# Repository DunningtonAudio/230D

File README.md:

# 230D
A triple envelope follower project

The 230D Triple Envelope Follower is designed to replicate the functionality of the Buchla 230A module using modern construction techniques and readily available parts. It is primarily based on the original circuit designed by Don Buchla, with the following additions/alterations:

* Proper current limiting implemented for pulse output LEDs, increasing LED life and preventing crosstalk between channels
* Pulse/gate output voltages adjusted to 10V/5V
* Pulse outputs are buffered, protecting the passive pulse generation network from the effects of loading when stacking one output to multiple destinations
* Pulse outputs are designed to allow stacking of multiple outputs to a single input, whilst also being able to drive a floating input low.

The repository contains:

* KiCad project files
* Schematic and build/calibration notes as PDF files
* Bill of Materials in ODS and PDF format
* Interactive webpage for matching BOM items to PCB locations

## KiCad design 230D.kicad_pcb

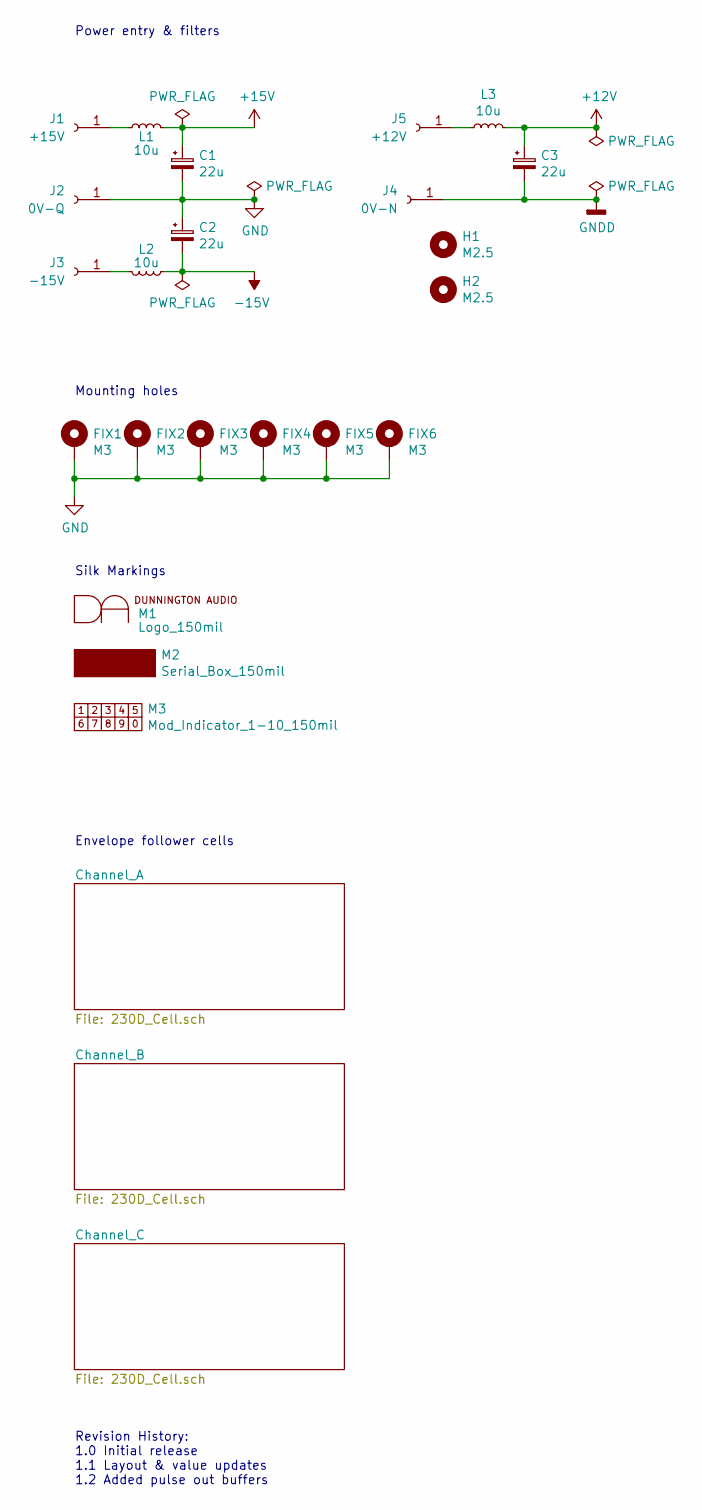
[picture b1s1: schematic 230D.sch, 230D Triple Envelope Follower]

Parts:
C1, C2, C3: 22u; CP_Elec_5x5.3
FIX1, FIX2, FIX3, FIX4, FIX5, FIX6: M3; MountingHole_3.2mm_M3_Pad_Via
H1, H2: M2.5; MountingHole_2.5mm
J1: +15V; SolderWirePad_1x01_Drill1.2mm
J2: 0V-Q; SolderWirePad_1x01_Drill1.2mm
J3: -15V; SolderWirePad_1x01_Drill1.2mm
J4: 0V-N; SolderWirePad_1x01_Drill1.2mm
J5: +12V; SolderWirePad_1x01_Drill1.2mm
L1, L2, L3: 10u; L_0805_2012Metric
M1: Logo_150mil
M2: Serial_Box_150mil
M3: Mod_Indicator_1-10_150mil

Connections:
+12V: C3.1, L3.2; also elsewhere on the board
+15V: C1.1, L1.2; also elsewhere on the board
-15V: C2.2, L2.1; also elsewhere on the board
GND: C1.2, C2.1, FIX1.1, FIX2.1, FIX3.1, FIX4.1, FIX5.1, FIX6.1, J2.1; also elsewhere on the board
GNDD: C3.2, J4.1; also elsewhere on the board
unnamed: J1.1, L1.1
unnamed: J3.1, L2.2
unnamed: J5.1, L3.1

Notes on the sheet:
Power entry & filters
Mounting holes
Silk Markings
Envelope follower cells
Revision History: 1.0 Initial release 1.1 Layout & value updates 1.2 Added pulse out buffers

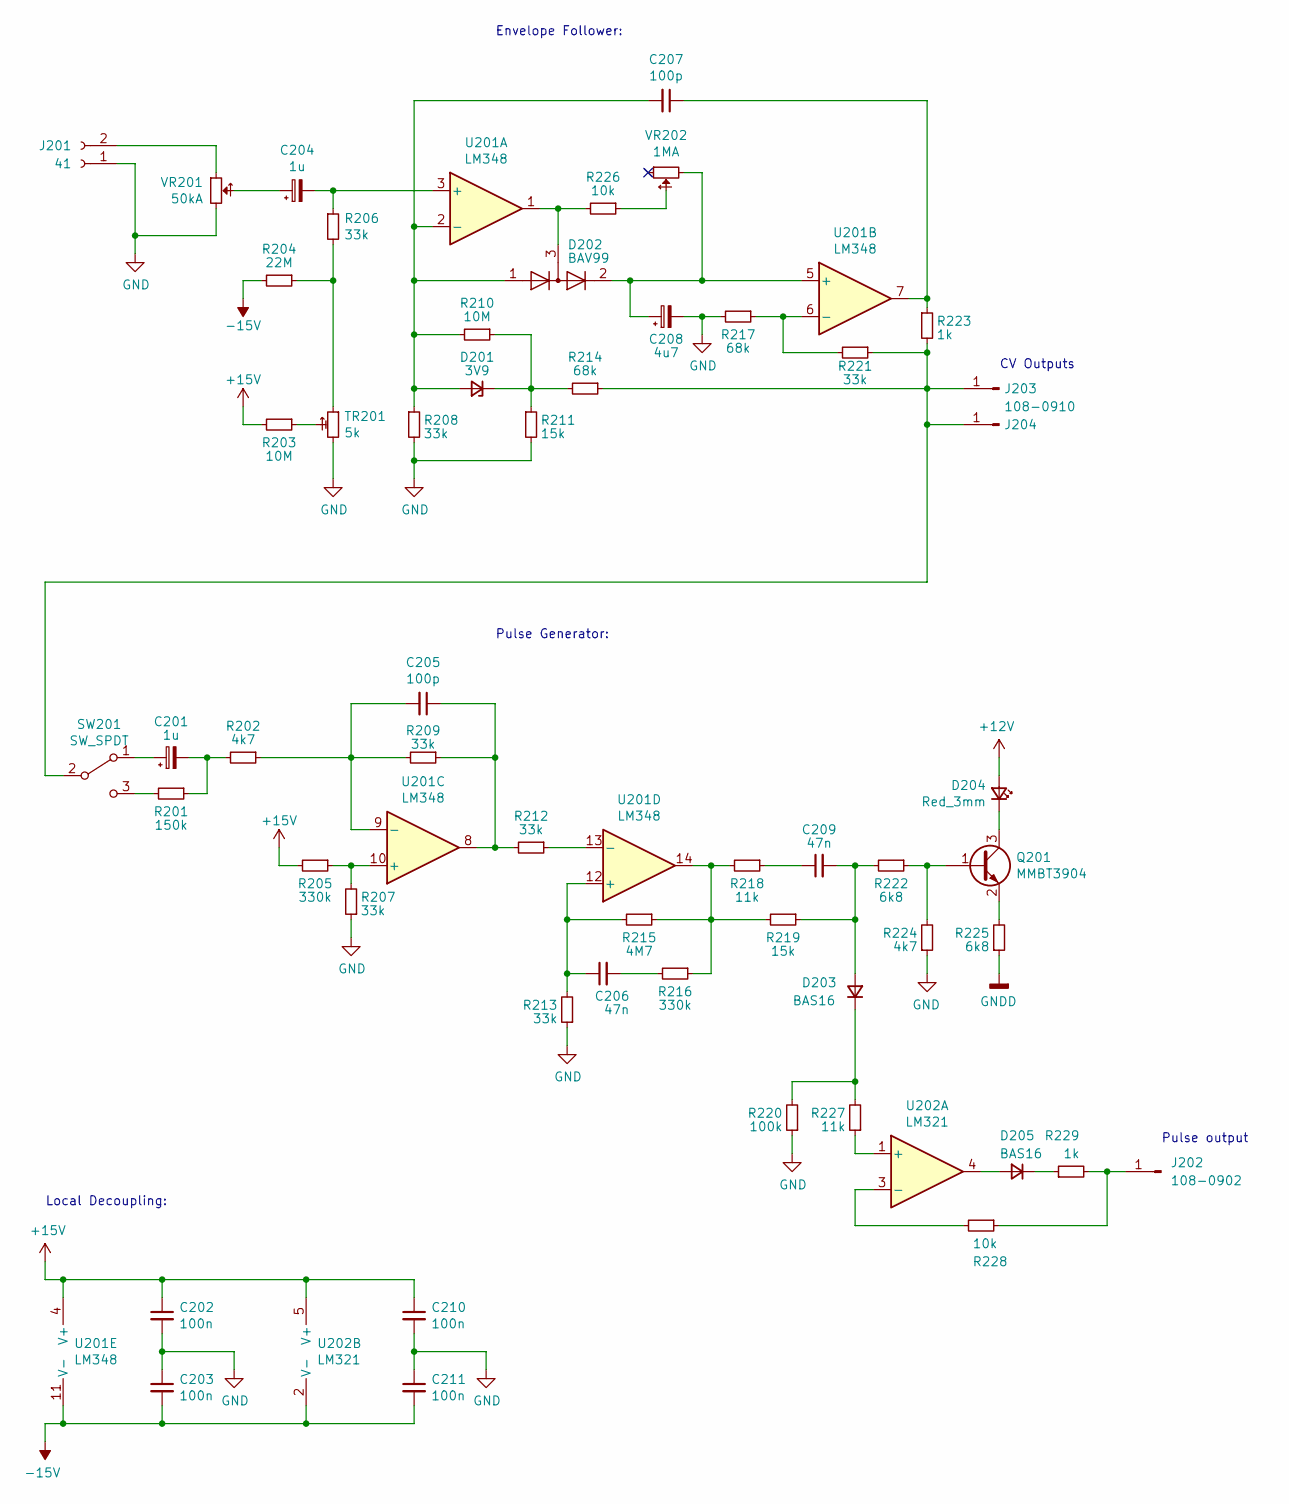
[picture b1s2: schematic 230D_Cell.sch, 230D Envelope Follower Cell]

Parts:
C101, C104: 1u; CP_Elec_4x5.3
C102, C103, C110, C111: 100n; C_0805_2012Metric
C105, C107: 100p; C_0805_2012Metric
C106, C109: 47n; C_0805_2012Metric
C108: 4u7; CP_EIA-3528-21_Kemet-B
D101: 3V9; D_SOD-323
D102: BAV99; SOT-23
D103, D105: BAS16; SOT-23
D104: Red_3mm; LED_D3.0mm
J101: 41; Switchcraft_41
J102: 108-0902; Johnson_108-09XX-001
J103, J104: 108-0910; Johnson_108-09XX-001
Q101: MMBT3904; SOT-23
R101: 150k; R_0805_2012Metric
R102, R124: 4k7; R_0805_2012Metric
R103, R110: 10M; R_0805_2012Metric
R104: 22M; R_0805_2012Metric
R105, R116: 330k; R_0805_2012Metric
R106, R107, R108, R109, R112, R113, R121: 33k; R_0805_2012Metric
R111, R119: 15k; R_0805_2012Metric
R114, R117: 68k; R_0805_2012Metric
R115: 4M7; R_0805_2012Metric
R118, R127: 11k; R_0805_2012Metric
R120: 100k; R_0805_2012Metric
R122, R125: 6k8; R_0805_2012Metric
R123, R129: 1k; R_0805_2012Metric
R126, R128: 10k; R_0805_2012Metric
SW101: SW_SPDT; M201xSS1x01
TR101: 5k; Potentiometer_Bourns_3314J_Vertical
U101: LM348; SOIC-14_3.9x8.7mm_P1.27mm
U102: LM321; SOT-23-5
VR101: 50kA; RV16AF-41-(L)R1-XXX
VR102: 1MA; RV16AF-41-(L)R1-XXX

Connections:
+12V: D104.2 (A); also elsewhere on the board
+15V: C102.1, C110.1, R103.2, R105.2, U101.4 (V+), U102.5 (V+); also elsewhere on the board
-15V: C103.2, C111.2, R104.2, U101.11 (V-), U102.2 (V-); also elsewhere on the board
GND: C102.2, C103.1, C108.2, C110.2, C111.1, J101.1, R107.1, R108.2, R111.2, R113.1, R117.2, R120.1, R124.1, TR101.1, VR101.1; also elsewhere on the board
GNDD: R125.1; also elsewhere on the board
unnamed: C101.1, SW101.1 (A)
unnamed: C101.2, R101.1, R102.2
unnamed: C104.1, VR101.2
unnamed: C104.2, R106.1, U101.3 (+)
unnamed: C105.1, R109.1, R112.2, U101.8
unnamed: C105.2, R102.1, R109.2, U101.9 (-)
unnamed: C106.1, R113.2, R115.2, U101.12 (+)
unnamed: C106.2, R116.2
unnamed: C107.1, R123.1, U101.7
unnamed: C107.2, D101.2 (A), D102.1 (K), R108.1, R110.2, U101.2 (-)
unnamed: C108.1, D102.2 (A), U101.5 (+), VR102.1
unnamed: C109.1, R118.1
unnamed: C109.2, D103.1 (A), R119.1, R122.2
unnamed: D101.1 (K), R110.1, R111.1, R114.2
unnamed: D102.3 (K), R126.2, U101.1
unnamed: D103.3 (K), R120.2, R127.2
unnamed: D104.1 (K), Q101.3 (C)
unnamed: D105.1 (A), U102.4
unnamed: D105.3 (K), R129.1
unnamed: J101.2, VR101.3
unnamed: J102.1, R128.1, R129.2
unnamed: J103.1, J104.1, R114.1, R121.1, R123.2, SW101.2 (B)
unnamed: Q101.1 (B), R122.1, R124.2
unnamed: Q101.2 (E), R125.2
unnamed: R101.2, SW101.3 (C)
unnamed: R103.1, TR101.2
unnamed: R104.1, R106.2, TR101.3
unnamed: R105.1, R107.2, U101.10 (+)
unnamed: R112.1, U101.13 (-)
unnamed: R115.1, R116.1, R118.2, R119.2, U101.14
unnamed: R117.1, R121.2, U101.6 (-)
unnamed: R126.1, VR102.2
unnamed: R127.1, U102.1 (+)
unnamed: R128.2, U102.3 (-)

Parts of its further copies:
C201, C204, C301, C304: 1u; CP_Elec_4x5.3
C202, C203, C210, C211, C302, C303, C310, C311: 100n; C_0805_2012Metric
C205, C207, C305, C307: 100p; C_0805_2012Metric
C206, C209, C306, C309: 47n; C_0805_2012Metric
C208, C308: 4u7; CP_EIA-3528-21_Kemet-B
D201, D301: 3V9; D_SOD-323
D202, D302: BAV99; SOT-23
D203, D205, D303, D305: BAS16; SOT-23
D204, D304: Red_3mm; LED_D3.0mm
J201, J301: 41; Switchcraft_41
J202, J302: 108-0902; Johnson_108-09XX-001
J203, J204, J303, J304: 108-0910; Johnson_108-09XX-001
Q201, Q301: MMBT3904; SOT-23
R201, R301: 150k; R_0805_2012Metric
R202, R224, R302, R324: 4k7; R_0805_2012Metric
R203, R210, R303, R310: 10M; R_0805_2012Metric
R204, R304: 22M; R_0805_2012Metric
R205, R216, R305, R316: 330k; R_0805_2012Metric
R206, R207, R208, R209, R212, R213, R221, R306, R307, R308, R309, R312, R313, R321: 33k; R_0805_2012Metric
R211, R219, R311, R319: 15k; R_0805_2012Metric
R214, R217, R314, R317: 68k; R_0805_2012Metric
R215, R315: 4M7; R_0805_2012Metric
R218, R227, R318, R327: 11k; R_0805_2012Metric
R220, R320: 100k; R_0805_2012Metric
R222, R225, R322, R325: 6k8; R_0805_2012Metric
R223, R229, R323, R329: 1k; R_0805_2012Metric
R226, R228, R326, R328: 10k; R_0805_2012Metric
SW201, SW301: SW_SPDT; M201xSS1x01
TR201, TR301: 5k; Potentiometer_Bourns_3314J_Vertical
U201, U301: LM348; SOIC-14_3.9x8.7mm_P1.27mm
U202, U302: LM321; SOT-23-5
VR201, VR301: 50kA; RV16AF-41-(L)R1-XXX
VR202, VR302: 1MA; RV16AF-41-(L)R1-XXX

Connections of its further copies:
+12V: D204.2 (A), D304.2 (A); also elsewhere on the board
+15V: C202.1, C210.1, C302.1, C310.1, R203.2, R205.2, R303.2, R305.2, U201.4 (V+), U202.5 (V+), U301.4 (V+), U302.5 (V+); also elsewhere on the board
-15V: C203.2, C211.2, C303.2, C311.2, R204.2, R304.2, U201.11 (V-), U202.2 (V-), U301.11 (V-), U302.2 (V-); also elsewhere on the board
GND: C202.2, C203.1, C208.2, C210.2, C211.1, C302.2, C303.1, C308.2, C310.2, C311.1, J201.1, J301.1, R207.1, R208.2, R211.2, R213.1, R217.2, R220.1, R224.1, R307.1, R308.2, R311.2, R313.1, R317.2, R320.1, R324.1, TR201.1, TR301.1, VR201.1, VR301.1; also elsewhere on the board
GNDD: R225.1, R325.1; also elsewhere on the board
unnamed: C201.1, SW201.1 (A)
unnamed: C201.2, R201.1, R202.2
unnamed: C204.1, VR201.2
unnamed: C204.2, R206.1, U201.3 (+)
unnamed: C205.1, R209.1, R212.2, U201.8
unnamed: C205.2, R202.1, R209.2, U201.9 (-)
unnamed: C206.1, R213.2, R215.2, U201.12 (+)
unnamed: C206.2, R216.2
unnamed: C207.1, R223.1, U201.7
unnamed: C207.2, D201.2 (A), D202.1 (K), R208.1, R210.2, U201.2 (-)
unnamed: C208.1, D202.2 (A), U201.5 (+), VR202.1
unnamed: C209.1, R218.1
unnamed: C209.2, D203.1 (A), R219.1, R222.2
unnamed: C301.1, SW301.1 (A)
unnamed: C301.2, R301.1, R302.2
unnamed: C304.1, VR301.2
unnamed: C304.2, R306.1, U301.3 (+)
unnamed: C305.1, R309.1, R312.2, U301.8
unnamed: C305.2, R302.1, R309.2, U301.9 (-)
unnamed: C306.1, R313.2, R315.2, U301.12 (+)
unnamed: C306.2, R316.2
unnamed: C307.1, R323.1, U301.7
unnamed: C307.2, D301.2 (A), D302.1 (K), R308.1, R310.2, U301.2 (-)
unnamed: C308.1, D302.2 (A), U301.5 (+), VR302.1
unnamed: C309.1, R318.1
unnamed: C309.2, D303.1 (A), R319.1, R322.2
unnamed: D201.1 (K), R210.1, R211.1, R214.2
unnamed: D202.3 (K), R226.2, U201.1
unnamed: D203.3 (K), R220.2, R227.2
unnamed: D204.1 (K), Q201.3 (C)
unnamed: D205.1 (A), U202.4
unnamed: D205.3 (K), R229.1
unnamed: D301.1 (K), R310.1, R311.1, R314.2
unnamed: D302.3 (K), R326.2, U301.1
unnamed: D303.3 (K), R320.2, R327.2
unnamed: D304.1 (K), Q301.3 (C)
unnamed: D305.1 (A), U302.4
unnamed: D305.3 (K), R329.1
unnamed: J201.2, VR201.3
unnamed: J202.1, R228.1, R229.2
unnamed: J203.1, J204.1, R214.1, R221.1, R223.2, SW201.2 (B)
unnamed: J301.2, VR301.3
unnamed: J302.1, R328.1, R329.2
unnamed: J303.1, J304.1, R314.1, R321.1, R323.2, SW301.2 (B)
unnamed: Q201.1 (B), R222.1, R224.2
unnamed: Q201.2 (E), R225.2
unnamed: Q301.1 (B), R322.1, R324.2
unnamed: Q301.2 (E), R325.2
unnamed: R201.2, SW201.3 (C)
unnamed: R203.1, TR201.2
unnamed: R204.1, R206.2, TR201.3
unnamed: R205.1, R207.2, U201.10 (+)
unnamed: R212.1, U201.13 (-)
unnamed: R215.1, R216.1, R218.2, R219.2, U201.14
unnamed: R217.1, R221.2, U201.6 (-)
unnamed: R226.1, VR202.2
unnamed: R227.1, U202.1 (+)
unnamed: R228.2, U202.3 (-)
unnamed: R301.2, SW301.3 (C)
unnamed: R303.1, TR301.2
unnamed: R304.1, R306.2, TR301.3
unnamed: R305.1, R307.2, U301.10 (+)
unnamed: R312.1, U301.13 (-)
unnamed: R315.1, R316.1, R318.2, R319.2, U301.14
unnamed: R317.1, R321.2, U301.6 (-)
unnamed: R326.1, VR302.2
unnamed: R327.1, U302.1 (+)
unnamed: R328.2, U302.3 (-)

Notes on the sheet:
Envelope Follower:
Pulse Generator:
Local Decoupling:
CV Outputs
Pulse output

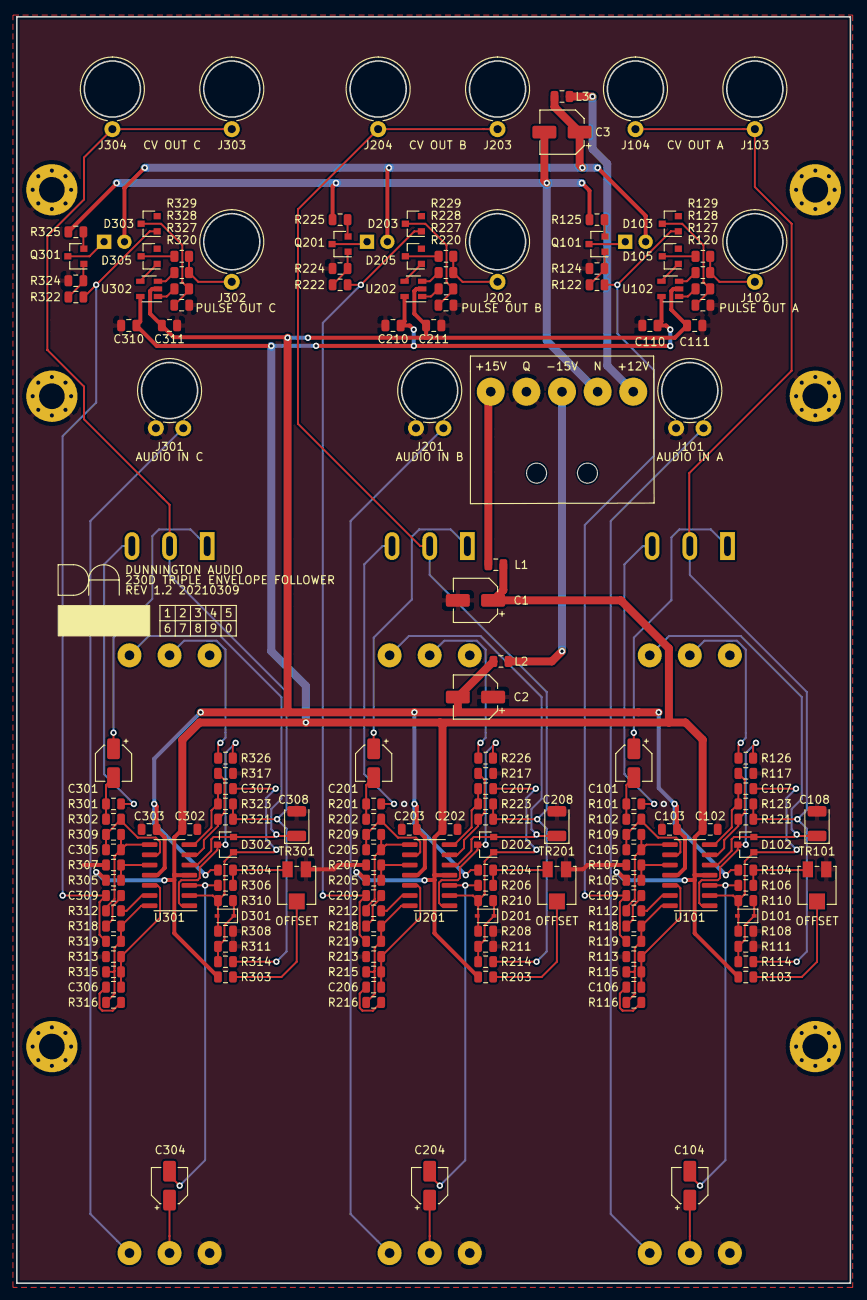
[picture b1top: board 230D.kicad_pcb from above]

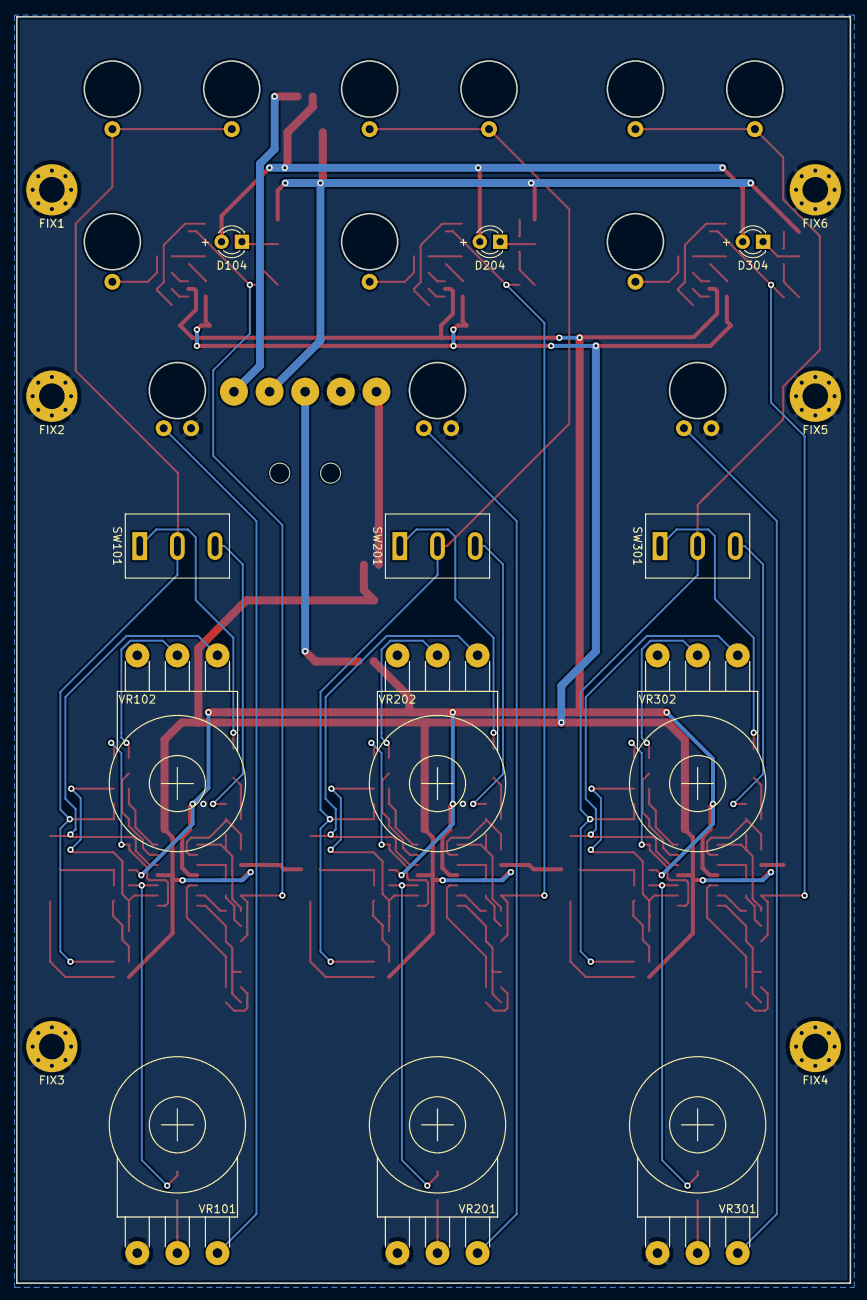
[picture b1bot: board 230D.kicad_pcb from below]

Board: 2 copper layers, 104.0 x 158.0 mm, 190 parts (18 on the bottom side), 110 nets.

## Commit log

2021-12-06 Readme update
2022-12-09 BOM correction
